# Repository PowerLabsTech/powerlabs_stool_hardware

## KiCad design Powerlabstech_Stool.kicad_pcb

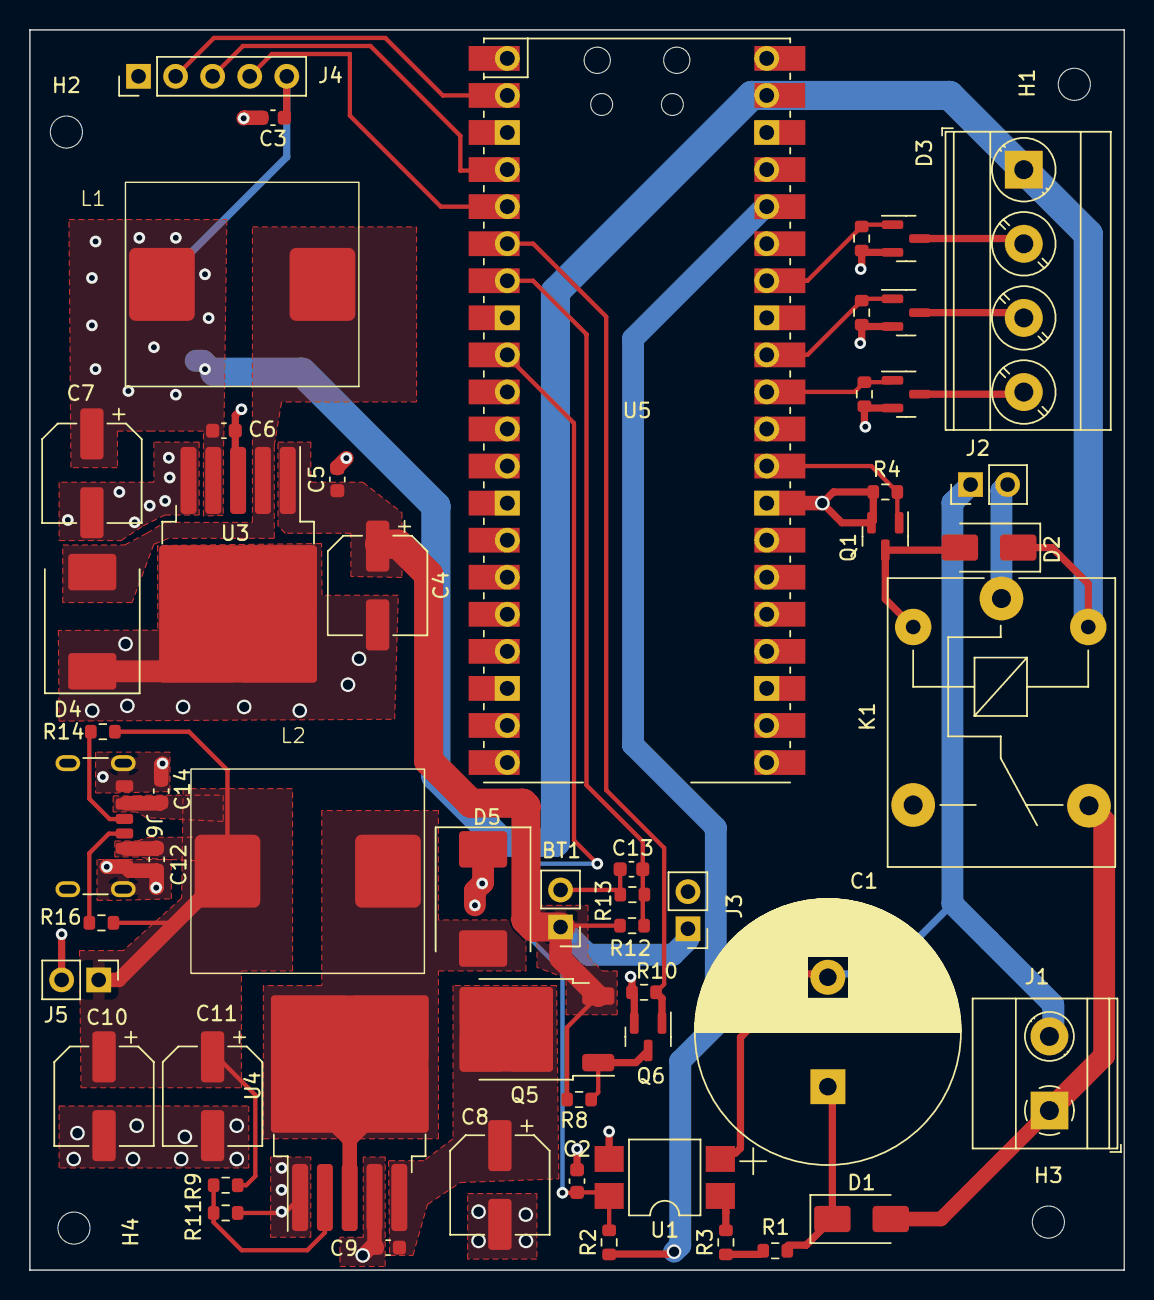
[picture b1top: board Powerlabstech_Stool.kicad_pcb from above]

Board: 2 copper layers, 75.0 x 85.0 mm, 58 parts (0 on the bottom side), 32 nets.

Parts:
BT1: Battery; PinHeader_1x02_P2.54mm_Vertical
C1: 120uF/450v; CP_Radial_D18.0mm_P7.50mm
C2, C3, C5, C6, C9, C12, C13, C14: 100nF; C_0603_1608Metric
C4, C7, C8, C10, C11: 470uF; CP_Elec_6.3x7.7
D1, D2: D; D_SMA
D3: LED_ARGB; TerminalBlock_Phoenix_MKDS-3-4-5.08_1x04_P5.08mm_Horizontal
D4, D5: B540C; D_SMC
H1, H2, H3, H4: MountingHole; MountingHole_2.2mm_M2
J1: Screw_Terminal_01x02; TerminalBlock_Phoenix_MKDS-1,5-2-5.08_1x02_P5.08mm_Horizont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
J2, J3: Conn_01x02_Pin; PinHeader_1x02_P2.54mm_Vertical
J4: Conn_01x05_Socket; PinHeader_1x05_P2.54mm_Vertical
J5: Screw_Terminal_01x02; PinHeader_1x02_P2.54mm_Vertical
J6: USB_C_Receptacle_PowerOnly_6P; USB_C_Receptacle_GCT_USB4125-xx-x_6P_TopMnt_Horizontal
K1: SANYOU_SRD_Form_C; Relay_SPDT_SANYOU_SRD_Series_Form_C
L1, L2: 47uH; SMD,13.7x12.8mm
Q1, Q2, Q3, Q4, Q6: Q_NMOS_GSD; SOT-23
Q5: Q_NMOS_GDS; TO-252-2
R1, R2, R3, R4, R5, R6, R7, R8, R9, R10, R13, R14, R16: 10K; R_0603_1608Metric
R11: 3K3; R_0603_1608Metric
R12: 47k; R_0603_1608Metric
U1: PC817; SMDIP-4_W7.62mm
U3: LM2596S-5; TO-263-5_TabPin3
U4: XL4015; TO-263-5_TabPin3
U5: SC0915; RPi_Pico_SMD_TH_REMOVED_SWD_PINS

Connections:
+3.3V: R2.1, U5.36 (3V3_OUT)
+5V: C3.1, C6.1, C7.1, D2.1 (K), D3.1 (A), J4.5, K1.5, L1.2, U3.4 (FB), U5.39 (VSYS)
/BATT_OUT+: C8.1, C9.1, Q5.2 (D), U4.5 (VIN)
/BATT_POS: BT1.1 (+), C4.1, C5.1, J3.1, Q5.3 (S), R8.1, R12.1, U3.1 (VIN)
/BATT_READ: C13.1, R12.2, R13.1, U5.7 (GP5)
/FB_1: R9.2, R11.1, U4.2 (FB)
/GSM_RESET: J4.4, U5.5 (GP3)
/GSM_RXD: J4.3, U5.4 (GP2)
/GSM_TXD: J4.2, U5.2 (GP1)
/LED_BLUE: Q4.1 (G), R7.1, U5.31 (GP26)
/LED_BLUE_OUT: D3.4 (BK), Q4.3 (D)
/LED_GREEN: Q3.1 (G), R6.1, U5.32 (GP27)
/LED_GREEN_OUT: D3.3 (GK), Q3.3 (D)
/LED_RED: Q2.1 (G), R5.1, U5.34 (GP28)
/LED_RED_OUT: D3.2 (RK), Q2.3 (D)
/LIVE: D1.2 (A), J1.1, K1.4
/LIVE_RELAY_CHARGER_OUT: J2.2, K1.1
/LOAD_SWITCH: Q6.1 (G), R10.1, U5.6 (GP4)
/MAINS_RELAY: Q1.1 (G), R4.1, U5.29 (GP22)
/MAINS_SENSE: C2.1, R2.2, U1.4, U5.9 (GP6)
/NEUTRAL: C1.2, J1.2, J2.1, U1.2
/main_det_ret: C1.1, D1.1 (K), R1.1
/out_1: D4.2 (A), L1.1, U3.2 (OUT)
/sw_1: D5.2 (A), L2.1, U4.3 (SW)
/sw_OUT: C10.1, C11.1, C12.1, C14.1, J5.1, J6.A9 (VBUS), J6.B9 (VBUS), L2.2, R9.1, R14.1, R16.1
GND: BT1.2 (-), C2.2, C3.2, C4.2, C5.2, C6.2, C7.2, C8.2, C9.2, C10.2, C11.2, C12.2, C13.2, C14.2, D4.1 (K), D5.1 (K), J3.2, J4.1, J5.2, J6.A12 (GND), J6.B12 (GND), J6.S1 (SHIELD), Q1.2 (S), Q2.2 (S), Q3.2 (S), Q4.2 (S), Q6.2 (S), R4.2, R5.2, R6.2, R7.2, R10.2, R11.2, R13.2, U1.3, U3.3 (GND), U3.5 (~ON/OFF), U4.1 (GND), U4.4 (VC), U5.3 (GND), U5.13 (GND), U5.18 (GND), U5.23 (GND), U5.28 (GND), U5.33 (AGND)
unnamed: D2.2 (A), K1.2, Q1.3 (D)
unnamed: J6.A5 (CC1), R14.2
unnamed: J6.B5 (CC2), R16.2
unnamed: Q5.1 (G), Q6.3 (D), R8.2
unnamed: R1.2, R3.1
unnamed: R3.2, U1.1

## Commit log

2024-02-01 First design files
2024-02-03 Added the USB output and added the output files
2024-02-04 Modified USB type C to supply 3A current
